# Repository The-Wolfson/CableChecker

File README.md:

# Cable Checker
A handheld device to check XLR3 cables faster.

## Basic Operation
This device has 3 testing modes:
- input (tests incoming signal)
- output (tests outgoing signal)
- both (tests both incoming and outgoing signals)

These are controlled by the slide switch ion the side.

To start a test, hold the rotary encoder down for 3 seconds. The test will run for 5 seconds, afterwards the LEDs will show the results and input levels.

There is also a headphone jack, the knob can be used for volume.

When in output mode, the knob is used for volume.

## BOM

| Item | Model | Qty | Price (USD) | Shipping | Link |
|-|-|-|-|-|-|
| Audio Codec | ES8388 | 1 | $2.51 | $9.34 USD | [Link](https://lcsc.com/product-detail/ADCs-DACs-Special-Purpose_Everest-semi-Everest-Semiconductor-ES8388_C365736.html) |
| Audio Transformer | HR610660 | 2 | $1.03 | '' | [Link](https://lcsc.com/product-detail/Audio-Transformers_HANRUN-Zhongshan-HanRun-Elec-HR610660_C48357.html) |
| XLR3 Male | NC3MAAH | 1 | $1.57 | '' | [Link](https://lcsc.com/product-detail/XLR-Cannon-Connectors_Neutrik-NC3MAAH_C368463.html) |
| XLR3 Female | NC3FAAH | 1 | $1.43 | '' | [Link](https://lcsc.com/product-detail/XLR-Cannon-Connectors_Neutrik-NC3FAAH_C368521.html) |
| Audio Jack | PJ-306M | 1 | $1.14 | '' | [Link](https://lcsc.com/product-detail/Audio-Connectors_HOOYA-PJ-306M_C2939172.html) |
| Rotary Encoder w/ Button | PEC11R-4220F-S0024 | 1 | $2.80  | '' | [Link](https://lcsc.com/product-detail/Rotary-Encoders_BOURNS-PEC11R-4220F-S0024_C143797.html) |
| Slide Switch (SP3T) | SK13D07VG5 | 1 | $0.66 | '' | [Link](https://lcsc.com/product-detail/Slide-Switches_SHOU-HAN-SK13D07VG5_C393948.html) |
| Microcontroller | ESP32-S3-Zero | 1 | $6.06 | Free | [Link](https://core-electronics.com.au/esp32-s3-mini-development-board-retired.html) |
| LED Bar Graph | WS2812B | 1 | $3.19 | '' | [Link](https://core-electronics.com.au/glowbit-stick-1x8.html) |
| Encoder Knob | ADA5093 | 1 | $1.17 | '' | [Link](https://core-electronics.com.au/slim-rubber-rotary-encoder-knob-11-5mm-x-14-5mm-d-shaft.html) |
| PCB (JLCPCB) | - | 5 | $2 | $16.59 AUD | [Link](https://jlcpcb.com) |
| PCB Assembly (for ES8388) | - | 2 | $15.40 | '' | [Link](https://jlcpcb.com) |
| Case (Print Legion) | - | 1 | $0 | $5 AUD | [Link](https://printlegion.hackclub.com) |

**AUD Total:** $98.46

**USD Total:** $62.35

## Background
I run sound at my school, and we have a legacy system, set up who knows how many years ago. As part of that, there are lots of XLR3 cables lying around that nobody knows if they work, or not.

The solution to my problem, a small portable device that tests if the XLR cable is functioning properly. THis exists... for around $350 AUD. 

So, when I heard about Hackclub's *Highway* YSWS, my mind immediately jumped to this.

## Additional Details
- I'm using a 14mmx55mmx2mm transparent acrylic sheet instead of the window print.

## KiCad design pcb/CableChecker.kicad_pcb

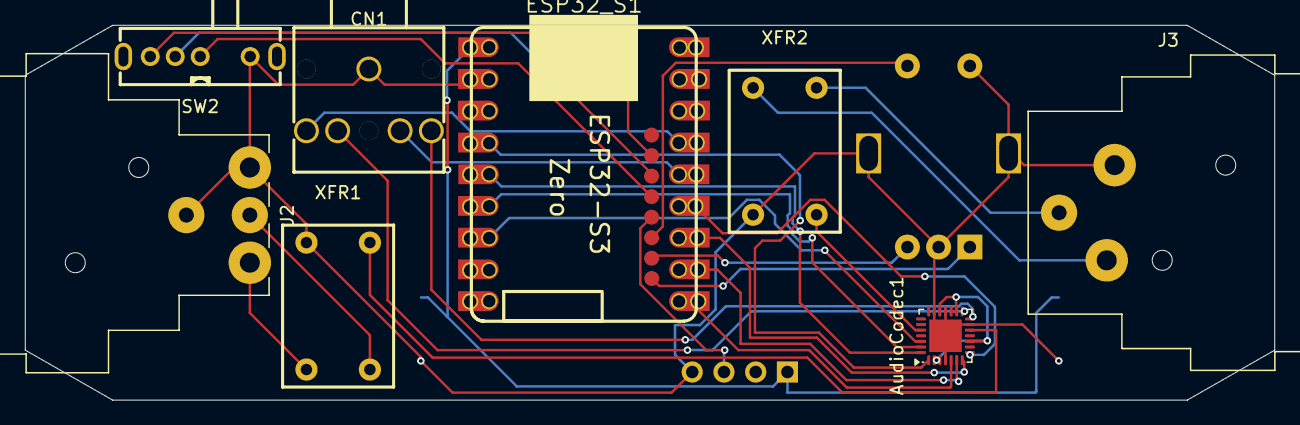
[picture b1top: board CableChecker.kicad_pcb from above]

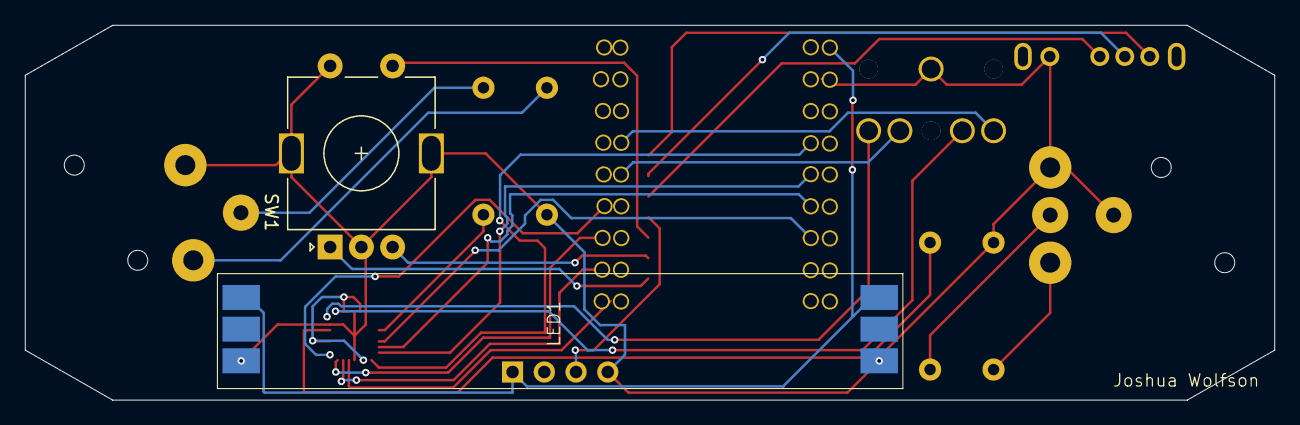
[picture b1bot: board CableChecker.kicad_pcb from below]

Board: 2 copper layers, 100.0 x 30.0 mm, 10 parts (2 on the bottom side), 28 nets.

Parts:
AudioCodec1: ES8388; QFN-28-1EP_4x4mm_P0.45mm_EP2.6x2.6mm
CN1: PJ-306M; AUDIO-TH_HOOYA_PJ-306M
ESP32_S1: ESP32-S3-ZERO
J2: NC3MAAH; Jack_XLR_Neutrik_NC3MAAH_Horizontal
J3: NC3FAAH; Jack_XLR_Neutrik_NC3FAAH_Horizontal
LED1: GlowbitL_LED_Strip_1x8
SW1: RotaryEncoder_Switch_MP; RotaryEncoder_Alps_EC11E-Switch_Vertical_H20mm
SW2: SW_SP3T; SW-TH_SK13D07VG5
XFR1, XFR2: HR610660; PWRM-TH_HR610660

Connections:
+3.3V: AudioCodec1.2 (DVDD), AudioCodec1.3 (PVDD), AudioCodec1.10 (VREF), AudioCodec1.16 (HPVDD), AudioCodec1.17 (AVDD), AudioCodec1.19 (ADCVREF)
+5V: ESP32_S1.5V, LED1.1
ASDOUT: AudioCodec1.8 (ASDOUT), ESP32_S1.10
CCLK: AudioCodec1.28 (CCLK), ESP32_S1.2
CDATA: AudioCodec1.27 (CDATA), ESP32_S1.3
CE: AudioCodec1.26 (CE), ESP32_S1.4
DSDIN: AudioCodec1.6 (DSDIN), ESP32_S1.8
GND: AudioCodec1.4 (DGND), AudioCodec1.13 (HPGND), AudioCodec1.18 (AGND), AudioCodec1.20 (VMID), AudioCodec1.29 (EPAD), CN1.1, ESP32_S1.GND, J2.1, J2.G, J3.1, LED1.3, LED1.4, SW1.C, SW1.MP, SW1.S2, SW2.1, XFR1.6, XFR2.5
LED-IN: ESP32_S1.39, LED1.3
LIN1: AudioCodec1.24 (LIN1), XFR2.1
LOUT1: AudioCodec1.12 (LOUT1), XFR1.2
LRCK: AudioCodec1.7 (LRCK), ESP32_S1.9
MCLK: AudioCodec1.1 (MCLK), ESP32_S1.1
unnamed: J2.2, XFR1.5
unnamed: J2.3, XFR1.1
unnamed: J3.2, XFR2.6
unnamed: J3.3, XFR2.2
RE-CLK: ESP32_S1.17, SW1.A
RE-DT: ESP32_S1.18, SW1.B
RE-SW: ESP32_S1.38, SW1.S1
Ring: AudioCodec1.14 (ROUT2), CN1.2
Ring-Shunt: CN1.3, ESP32_S1.11
SCLK: AudioCodec1.5 (SCLK), ESP32_S1.7
SW-1: ESP32_S1.40, SW2.2
SW-2: ESP32_S1.41, SW2.3
SW-3: ESP32_S1.42, SW2.4
Tip: AudioCodec1.15 (LOUT2), CN1.4
Tip-Shunt: CN1.5, ESP32_S1.12

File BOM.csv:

Part,SKU,Model,Quantity,Price (AUD),Price (USD),Shipping (AUD),Shipping (USD),Total (AUD),Total (USD),Link,
Audio Transformer,C48357,HR610660,2, $-   , $2.51 , $-   , $9.34 , $18.06 , $11.85 ,https://lcsc.com/product-detail/Audio-Transformers_HANRUN-Zh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,
Audio Codec,C365736,ES8388,1, $-   , $1.03 , $-   , ' , $1.57 , $1.03 ,https://lcsc.com/product-detail/ADCs-DACs-Special-Purpose_Ev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,
XLR3 Male,C368463,NC3MAAH,1, $-   , $1.57 , $-   , ' , $2.39 , $1.57 ,https://lcsc.com/product-detail/XLR-Cannon-Connectors_Neutri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,
XLR3 Female,C368521,NC3FAAH,1, $-   , $1.43 , $-   , ' , $2.18 , $1.43 ,https://lcsc.com/product-detail/XLR-Cannon-Connectors_Neutri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,
Audio Jack,C2939172,PJ-306M,5, $-   , $1.14 , $-   , ' , $1.74 , $1.14 ,https://lcsc.com/product-detail/Audio-Connectors_HOOYA-PJ-30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,
Slide Switch (SP3T),C393948,SK13D07VG5,20, $-   , $0.66 , $-   , ' , $1.01 , $0.66 ,https://lcsc.com/product-detail/Slide-Switches_SHOU-HAN-SK13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,
Microcontroller,WS-25081,ESP32-S3-Zero,1, $9.30 , $-   , $-   , $-   , $9.30 , $6.10 ,https://core-electronics.com.au/esp32-s3-mini-development-bo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,
Rotary Encoder w/ Button,ADA377,PEC11-4215F-S24,1, $9.95 , $-   , $-   , ' , $9.95 , $6.53 ,https://core-electronics.com.au/rotary-encoder-extras.html,
LED Bar Graph,CE08035,WS2812B,1, $4.90 , $-   , $-   , ' , $4.90 , $3.21 ,https://core-electronics.com.au/glowbit-stick-1x8.html,
Screws,,M2x38,,,,,, $-   , $-   ,,
Screws,,M1.6x12,,,,,, $-   , $-   ,,
PCB,JLCPCB,,, $3.18 , $-   , $16.59 , $-   , $19.77 , $12.97 ,,
Case,JLC3DP,,, $5.37 , $-   , ' , $-   , $5.37 , $3.52 ,,
Total,,,,,,,, $76.24 , $50.01 ,,

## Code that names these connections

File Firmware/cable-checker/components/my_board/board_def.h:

#ifndef _AUDIO_BOARD_DEFINITION_H_
#define _AUDIO_BOARD_DEFINITION_H_

// ES8388
///I2C
#define CCLK                2 //SCL
#define CDATA               3 //SDA
#define CE                  4
///I2S
#define MCLK                1
#define ASDOUT              10 //DOUT
#define LRCK                9 //WS
#define DSDIN               8 //DIN
#define SCLK                7 //BCLK

#define BUTTON_VOLUP_ID           -1     /* You need to define the GPIO pins of your board */
#define BUTTON_VOLDOWN_ID         -1     /* You need to define the GPIO pins of your board */
#define BUTTON_MUTE_ID            -1     /* You need to define the GPIO pins of your board */
#define BUTTON_SET_ID             -1     /* You need to define the GPIO pins of your board */
#define BUTTON_MODE_ID            -1     /* You need to define the GPIO pins of your board */
#define BUTTON_PLAY_ID            -1     /* You need to define the GPIO pins of your board */
#define PA_ENABLE_GPIO            -1     /* You need to define the GPIO pins of your board */
#define ADC_DETECT_GPIO           -1     /* You need to define the GPIO pins of your board */
#define BATTERY_DETECT_GPIO       -1     /* You need to define the GPIO pins of your board */
#define SDCARD_INTR_GPIO          -1     /* You need to define the GPIO pins of your board */

#define SDCARD_OPEN_FILE_NUM_MAX  -1

#define BOARD_PA_GAIN             (10) /* Power amplifier gain defined by board (dB) */

#define SDCARD_PWR_CTRL             -1
#define ESP_SD_PIN_CLK              -1
#define ESP_SD_PIN_CMD              -1
#define ESP_SD_PIN_D0               -1
#define ESP_SD_PIN_D1               -1
#define ESP_SD_PIN_D2               -1
#define ESP_SD_PIN_D3               -1
#define ESP_SD_PIN_D4               -1
#define ESP_SD_PIN_D5               -1
#define ESP_SD_PIN_D6               -1
#define ESP_SD_PIN_D7               -1
#define ESP_SD_PIN_CD               -1
#define ESP_SD_PIN_WP               -1

extern audio_hal_func_t AUDIO_NEW_CODEC_DEFAULT_HANDLE;

#define AUDIO_CODEC_DEFAULT_CONFIG(){                   \
        .adc_input  = AUDIO_HAL_ADC_INPUT_LINE1,        \
        .dac_output = AUDIO_HAL_DAC_OUTPUT_ALL,         \
        .codec_mode = AUDIO_HAL_CODEC_MODE_BOTH,        \
        .i2s_iface = {                                  \
            .mode = AUDIO_HAL_MODE_SLAVE,               \
            .fmt = AUDIO_HAL_I2S_NORMAL,                \
            .samples = AUDIO_HAL_48K_SAMPLES,           \
            .bits = AUDIO_HAL_BIT_LENGTH_16BITS,        \
        },                                              \
};

#define INPUT_KEY_NUM     0             /* You need to define the number of input buttons on your board */

#define INPUT_KEY_DEFAULT_INFO() {}

#endif

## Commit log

2025-06-23 Added BOM
2025-06-25 BOM Update
2025-07-09 started firmware
2025-07-09 schematics
2025-07-11 added adf
2025-07-13 hardware mostly done
2025-07-14 finished hardware
2025-07-14 journal
2025-07-14 updated window
2025-07-14 fixed issue with total price
2025-07-21 updated BOM
2025-07-21 added encoder knob
2025-07-22 fixed tolerances
2025-07-26 added drill files
